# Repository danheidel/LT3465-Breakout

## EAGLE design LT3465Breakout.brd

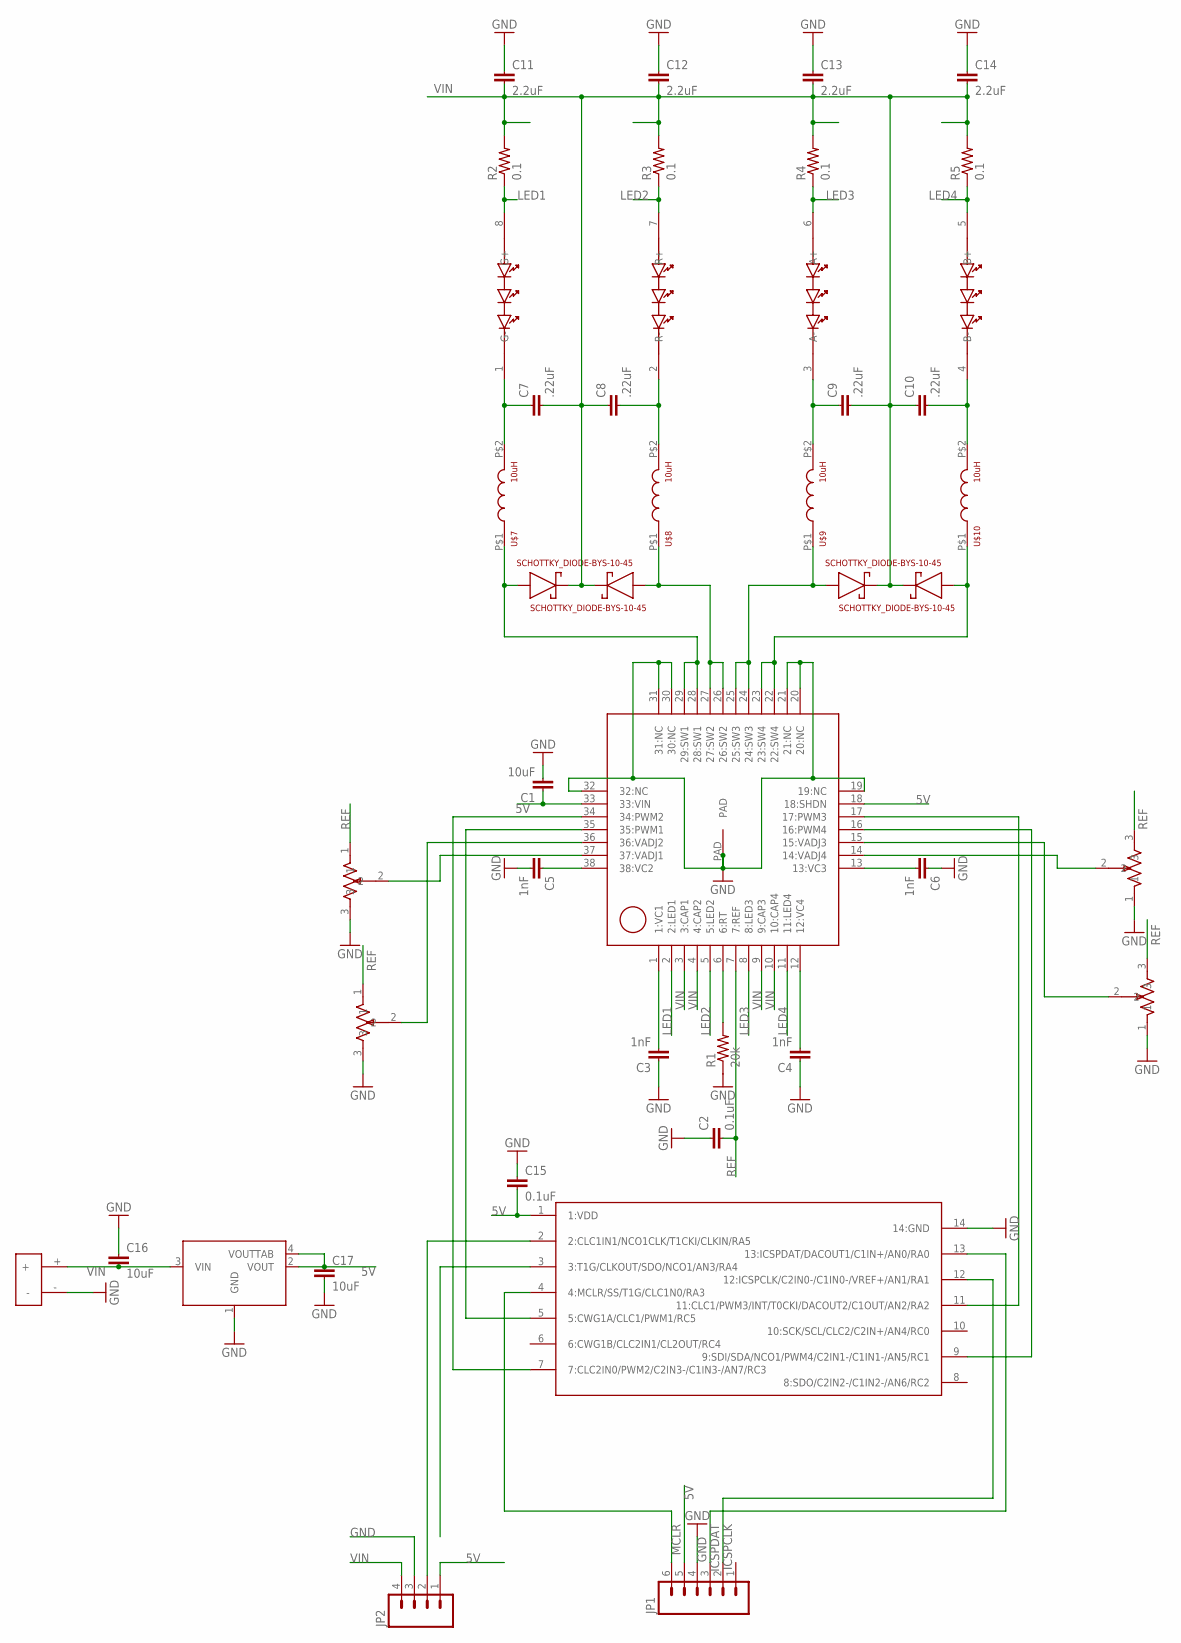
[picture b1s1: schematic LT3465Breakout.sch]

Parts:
C1: 10uF; 1210
C2, C15: 0.1uF; 0805
C3, C4, C5, C6: 1nF; 0805
C7, C8, C9, C10: .22uF; 0805
C11, C12, C13, C14: 2.2uF; 1206
C16, C17: 10uF; 1206
JP1: M06LOCK; 1X06_LOCK
JP2: M04LOCK; 1X04_LOCK
R1: 20k; 0805
R2, R3, R4, R5: 0.1; 1206
U$1: LT3476; QFN-38
U$2: PIC16F1503TSSOP14; TSSOP14
U$3, U$4, U$5, U$6: SCHOTTKY_DIODE-BYS-10-45; DO-214
U$7, U$8, U$9, U$10: 10uH; LQH88
U$11: LZC-00-MA00; LZC-00MA00
U$12, U$13, U$14, U$15: TRIMPOTTC33X-2; TC33X-2
U$16: 5V-LDO-ZLDO1117; ZLDO1117
U$17: POWER_SOLDER-1.5; POWER_SOLDER

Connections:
5V: C1.1, C15.2, C17.1, JP1.5, JP2.1, U$1.18 (18:SHDN), U$1.33 (33:VIN), U$2.1 (1:VDD), U$16.2 (VOUT), U$16.4 (VOUTTAB)
GND: C1.2, C2.1, C3.1, C4.1, C5.2, C6.1, C11.1, C12.1, C13.1, C14.1, C15.1, C16.1, C17.2, JP1.4, JP2.3, R1.1, U$1.19 (19:NC), U$1.20 (20:NC), U$1.21 (21:NC), U$1.30 (30:NC), U$1.31 (31:NC), U$1.32 (32:NC), U$1.PAD, U$2.14 (14:GND), U$12.3, U$13.3, U$14.1, U$15.1, U$16.1 (GND), U$17.-
ICSPCLK: JP1.2, U$2.12 (12:ICSPCLK/C2IN0-/C1IN0-/VREF+/AN1/RA1)
ICSPDAT: JP1.3, U$2.13 (13:ICSPDAT/DACOUT1/C1IN+/AN0/RA0)
LED1: R2.1, U$1.2 (2:LED1), U$11.8 (G+)
LED1B: C7.1, U$7.P$2, U$11.1 (G-)
LED2: R3.1, U$1.5 (5:LED2), U$11.7 (R+)
LED2B: C8.2, U$8.P$2, U$11.2 (R-)
LED3: R4.1, U$1.8 (8:LED3), U$11.6 (A+)
LED3B: C9.1, U$9.P$2, U$11.3 (A-)
LED4: R5.1, U$1.11 (11:LED4), U$11.5 (B+)
LED4B: C10.2, U$10.P$2, U$11.4 (B-)
MCLR: JP1.6, U$2.4 (4:MCLR/SS/T1G/CLC1N0/RA3)
unnamed: JP2.2, U$2.2 (2:CLC1IN1/NCO1CLK/T1CKI/CLKIN/RA5)
unnamed: R1.2, U$1.6 (6:RT)
unnamed: C3.2, U$1.1 (1:VC1)
unnamed: C4.2, U$1.12 (12:VC4)
unnamed: C5.1, U$1.38 (38:VC2)
unnamed: C6.2, U$1.13 (13:VC3)
PWM1: U$1.35 (35:PWM1), U$2.5 (5:CWG1A/CLC1/PWM1/RC5)
PWM2: U$1.34 (34:PWM2), U$2.7 (7:CLC2IN0/PWM2/C2IN3-/C1IN3-/AN7/RC3)
PWM3: U$1.17 (17:PWM3), U$2.11 (11:CLC1/PWM3/INT/T0CKI/DACOUT2/C1OUT/AN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)
PWM4: U$1.16 (16:PWM4), U$2.9 (9:SDI/SDA/NCO1/PWM4/C2IN1-/C1IN1-/AN5/R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)
REF: C2.2, U$1.7 (7:REF), U$12.1, U$13.1, U$14.3, U$15.3
SW1: U$1.28 (28:SW1), U$1.29 (29:SW1), U$3.P$2 (ANODE), U$7.P$1
SW2: U$1.26 (26:SW2), U$1.27 (27:SW2), U$4.P$2 (ANODE), U$8.P$1
SW3: U$1.24 (24:SW3), U$1.25 (25:SW3), U$5.P$2 (ANODE), U$9.P$1
SW4: U$1.22 (22:SW4), U$1.23 (23:SW4), U$6.P$2 (ANODE), U$10.P$1
VADJ1: U$1.37 (37:VADJ1), U$12.2
VADJ2: U$1.36 (36:VADJ2), U$13.2
VADJ3: U$1.15 (15:VADJ3), U$15.2
VADJ4: U$1.14 (14:VADJ4), U$14.2
VIN: C7.2, C8.1, C9.2, C10.1, C11.2, C12.2, C13.2, C14.2, C16.2, JP2.4, R2.2, R3.2, R4.2, R5.2, U$1.3 (3:CAP1), U$1.4 (4:CAP2), U$1.9 (9:CAP3), U$1.10 (10:CAP4), U$3.P$1 (CATHODE), U$4.P$1 (CATHODE), U$5.P$1 (CATHODE), U$6.P$1 (CATHODE), U$16.3 (VIN), U$17.+

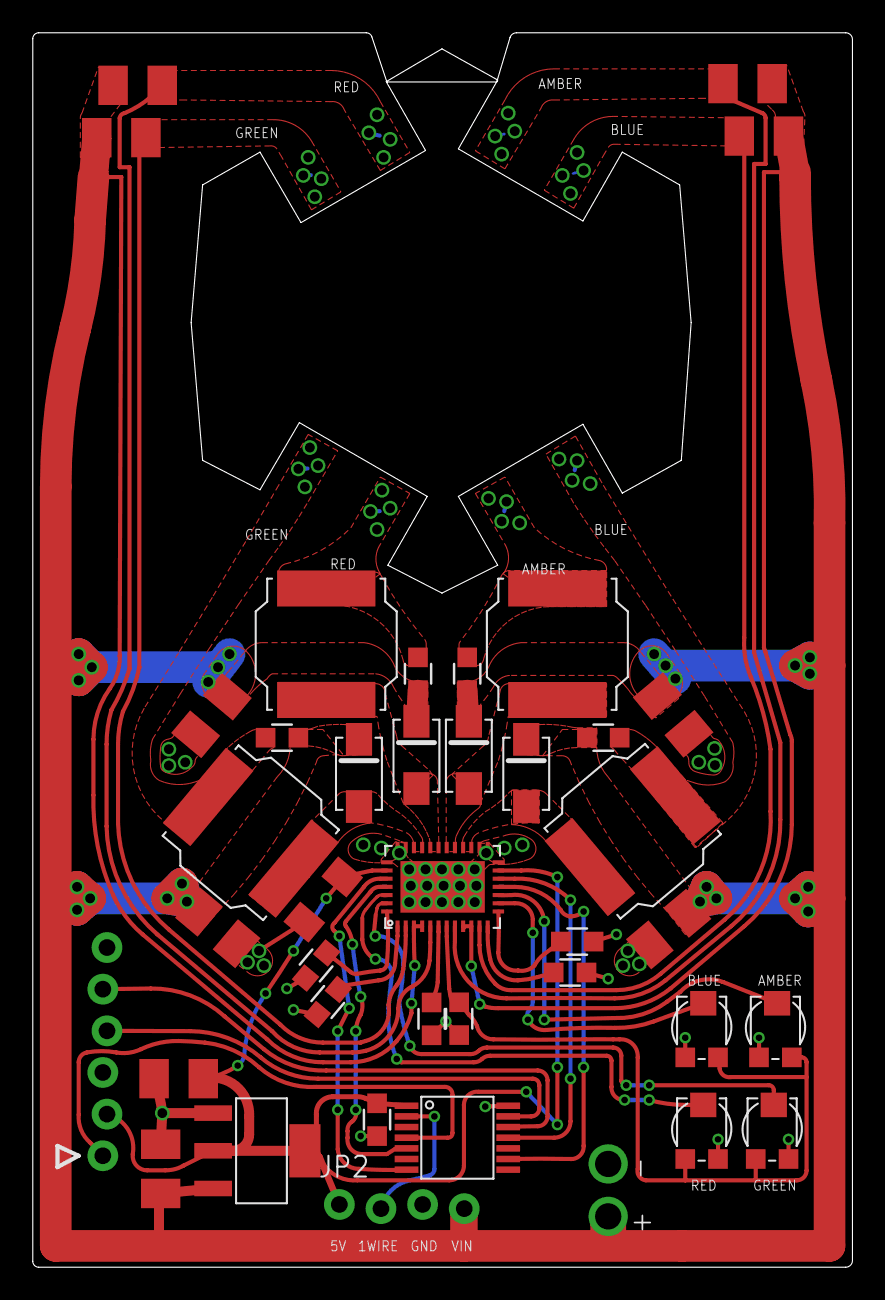
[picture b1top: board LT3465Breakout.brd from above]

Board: 2 copper layers, 50.0 x 75.3 mm, 41 parts (0 on the bottom side), 33 nets.

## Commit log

2011-12-24 LT3465 4-ch LED driver board with RGBA 40-watt LEDEngine emitter interface.
2012-03-05 Added comm header, general cleanup, more labels.
2012-03-08 Minor tweaks, addition of production files. First production run files here.
2012-03-08 Edited to be open at the top in last commit. New Gerbers.
2012-03-16 new .eps files.
2012-03-16 removed merge resolution files.
2012-03-17 Fixed errors in .eps files.
2012-04-26 .eps tweaks
